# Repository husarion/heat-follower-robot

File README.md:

# Heat Follower

## Description

**Heat Follower** is a project based on the ROSbot Pro platform, that follows heat by using a 360 degree thermal camera. It utilizes a MLX90641 sensor which is a 16x12 pixels IR sensor array. With some custom hardware it is possible to rotate this sensor and get a surround infrared image.

## Hardware

Hardware used in this project:
 - [ROSbot PRO](https://husarion.com/manuals/rosbot/#rosbot-pro)
 - [IR Thermal Sensor Array](https://www.melexis.com/en/product/mlx90641/high-operating-temperature-fir-thermal-sensor-array)
 - [Slip Ring](https://www.sparkfun.com/products/13064)
 - [Custom PCB designed in Eagle](https://github.com/husarion/heat-follower-robot/tree/main/CAD/PCB)
 - [Custom enclosure designed in Fusion 360](https://github.com/husarion/heat-follower-robot/tree/main/CAD)
 
## Software

### Thermal Camera

Software for Thermal Camera is written in [PlatformIO](https://platformio.org/) IDE to ensure compatibility with multiple platforms. MLX90641 [API](https://github.com/melexis/mlx90641-library) is used to ensure proper communication with the IR Sensor. It is slightly modified to support STM32's hardware.
Micro-ROS libraries are mandatory to communicate with ROSbot.

### ROS2 Python Node

A simple Python node was written to process the input thermal image with OpenCV and steer the robot. 
When a heat source is detected, this node sends rotational and linear velocities via `/cmd_vel` topic. 

### ROS Description

 Topic | Node Name | Description 
 --- | --- | ---
 `/thermal_image` | `/thermal_camera` | Raw thermal image represented with grayscale image (temperature = pixel intensity/100). 
 `/tc_image_devel` | `/thermal_subscriber`| Normalized image with target object contours. 
 `/tc_goal_angle` | `/thermal_subscriber`| Arrow marker pointing at the target angle relative to the robot. 
 
Additionally there are 3 parameters

 Parameter | Node Name | Type | Description
 ---  | --- | --- | ---
 `target_min_temp` | `/thermal_subscriber` | int | Minimum temperature of object 
 `target_max_temp` | `/thermal_subscriber` | int | Maximum temperature of object
 `go_to_hottest_piont` | `/thermal_subscriber` | bool | If true, robot follows the hottest object. If false, robot follows object which temperature is within `target_min_temp` and `target_max_temp`.
 
System schematic diagram:

The camera sends the main topic `/thermal_image` - a raw unprocessed image which is then transformed by `/thermal_subscriber` node. The transformed image published on `/tc_image_devel` containes a normalized image with a contour of an object selected by the algorithm. The angle of a selected object can also be visualized with `/tc_goal_angle` marker that publishes an arrow pointing from **base_link** to the direction of the object.

## Building the project

### Flashing MCU

Open the project with [Visual Studio Code](https://code.visualstudio.com/) with [PlatformIO](https://platformio.org/install/ide?install=vscode) plugin.

**This project is optimized for STM32F4 MCU's - keep that in mind when flashing on your hardware!**

After installing the **PlatformIO** extension to your VSCode, click its icon on the **Activity Bar** then from **Project Tasks** select **General** and **Upload**.

### Running on ROSbot

Clone **robot** folder to your ROSbot, connect the Thermal Camera via USB and run
```bash
cd robot/
docker-compose -f docker-compose.yaml up
```
After downloading all the necessary docker images ROSbot should follow warm objects nearby.

Due to issues connected with micro-ros agent, user must **unplug and plug** the Thermal Camera to reset the connection before running the docker compose. 
### Running Rviz on PC

Clone **pc** folder to your PC and run:

```bash
cd pc/
xhost local:root
docker-compose -f compose.pc.yaml up
```

Rviz should now pop up showing ROSbots surroundings in deep infrared.

If images are not visible click **Add** -> **By topic** -> **/thermal_image**

Here's ROSbot facing a kettle:

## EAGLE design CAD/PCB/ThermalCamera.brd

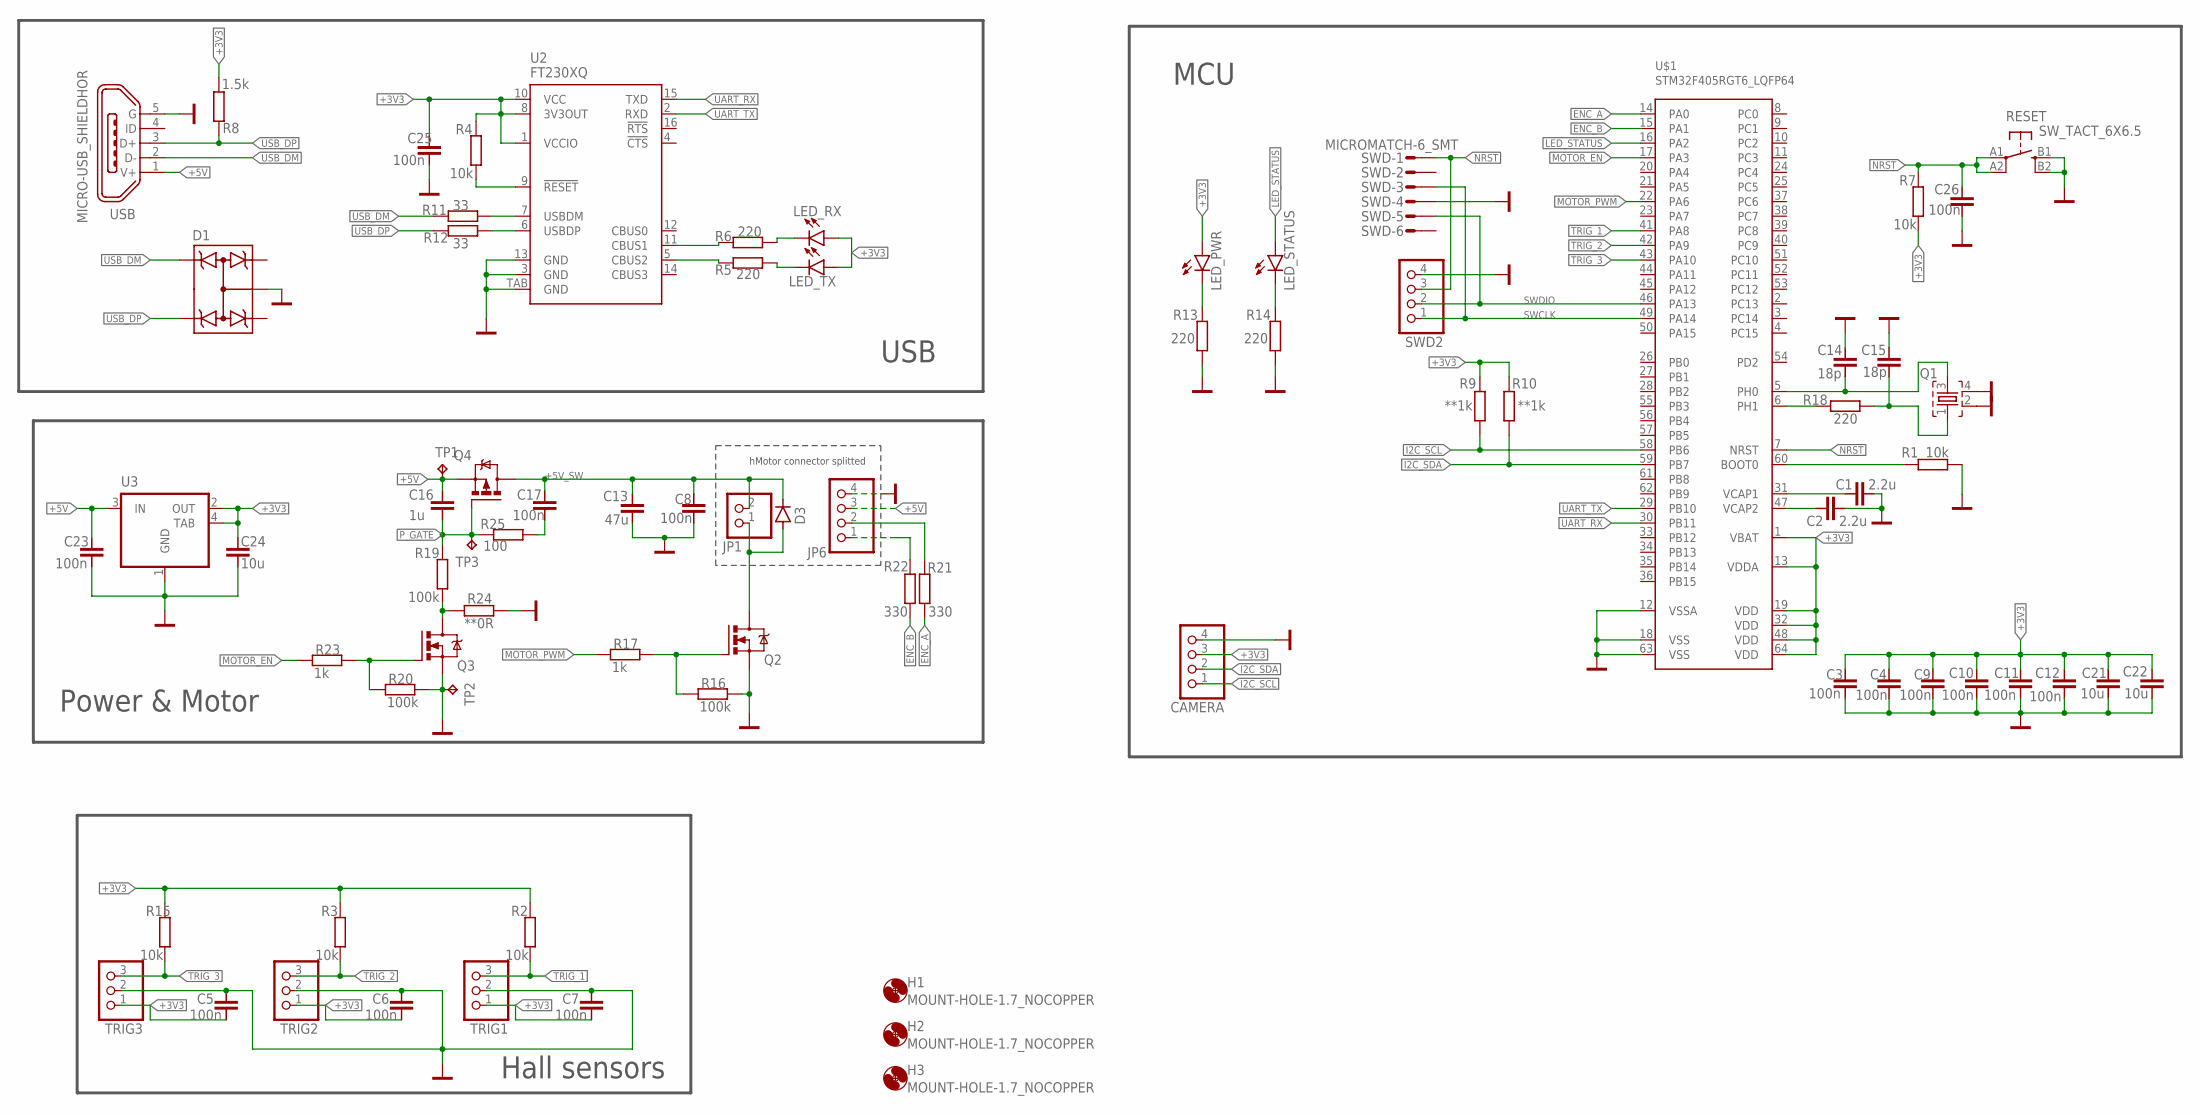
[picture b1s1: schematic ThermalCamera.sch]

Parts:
C1, C2: 2.2u; 0603
C3, C4, C5, C6, C7, C8, C9, C10, C11, C12, C17, C23, C25, C26: 100n; 0603
C13: 47u; 0805
C14, C15: 18p; 0603
C16: 1u; 0603
C21, C22, C24: 10u; 0603
CAMERA: PINHD-1X4; 1X04
D1: TRANSIL-4; SOT323-5
D3: BAR63-03; SOD323
H1, H2, H3: MOUNT-HOLE-1.7_NOCOPPER; 1.7-NO_COPPER
JP1: PINHD-1X2; 1X02
JP6: PINHD-1X4; 1X04
LED_PWR: LEDCHIPLED_0603; CHIPLED_0603
LED_RX: LEDCHIPLED_0603; CHIPLED_0603
LED_STATUS: LEDCHIPLED_0603; CHIPLED_0603
LED_TX: LEDCHIPLED_0603; CHIPLED_0603
Q1: CRYSTAL_4PIN-5X3.2; CRYSTAL_5X3.2_4PIN
Q2, Q3: NMOS-SOT23; SOT23
Q4: PMOS-SOT23; SOT23
R1, R2, R3, R4, R7, R15: 10k; 0603
R5, R6, R13, R14, R18: 220; 0603
R8: 1.5k; 0603
R9, R10: **1k; 0603
R11, R12: 33; 0603
R16, R19, R20: 100k; 0603
R17, R23: 1k; 0603
R21, R22: 330; 0603
R24: **0R; 0603
R25: 100; 0603
RESET: SW_TACT_6X6.5
SWD: MICROMATCH-6_SMT
SWD2: PINHD-1X4; 1X04
TP1, TP2: TPTP12R; TP12R
TP3: TPTP06R; TP06R
TRIG1, TRIG2, TRIG3: PINHD-1X3; 1X03
U2: FT230XQ; QFN16
U3: REG1117; SOT223
U$1: STM32F405RGT6_LQFP64; SQFP-S-10X10-64
USB: MICRO-USB_SHIELDHOR; MICRO_USB_6_SHIELD

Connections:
+3V3: C3.1, C4.1, C5.2, C6.2, C7.2, C9.1, C10.1, C11.1, C12.1, C21.1, C22.1, C24.1, C25.1, CAMERA.3, LED_PWR.A, LED_RX.A, LED_TX.A, R2.2, R3.2, R4.2, R7.1, R8.1, R9.2, R10.2, R15.2, TRIG1.1, TRIG2.1, TRIG3.1, U2.1 (VCCIO), U2.8 (3V3OUT), U2.10 (VCC), U3.2 (OUT), U3.4 (TAB), U$1.1 (VBAT), U$1.13 (VDDA), U$1.19 (VDD), U$1.32 (VDD), U$1.48 (VDD), U$1.64 (VDD)
+5V: C16.1, C23.1, JP6.3, Q4.2 (S), TP1.TP, U3.3 (IN), USB.1 (V+)
+5V_SW: C8.1, C13.1, C17.1, D3.1 (C), JP1.2, Q4.3 (D)
ENC_A: R21.2, U$1.14 (PA0)
ENC_B: R22.1, U$1.15 (PA1)
GND: C1.2, C2.2, C3.2, C4.2, C5.1, C6.1, C7.1, C8.2, C9.2, C10.2, C11.2, C12.2, C13.2, C14.1, C15.1, C21.2, C22.2, C23.2, C24.2, C25.2, C26.2, CAMERA.4, D1.2, JP6.4, Q1.2, Q1.4, Q2.2 (S), Q3.2 (S), R1.2, R13.2, R14.2, R16.1, R20.1, R24.1, RESET.B1 (S), RESET.B2 (S1), SWD.P$4, SWD2.4, TP2.TP, TRIG1.2, TRIG2.2, TRIG3.2, U2.3 (GND), U2.13 (GND), U2.TAB (GND), U3.1 (GND), U$1.12 (VSSA), U$1.18 (VSS), U$1.63 (VSS), USB.5 (G)
I2C_SCL: CAMERA.1, R9.1, U$1.58 (PB6)
I2C_SDA: CAMERA.2, R10.1, U$1.59 (PB7)
LED_STATUS: LED_STATUS.A, U$1.16 (PA2)
MOTOR_EN: R23.2, U$1.17 (PA3)
MOTOR_PWM: R17.2, U$1.22 (PA6)
unnamed: R1.1, U$1.60 (BOOT0)
unnamed: C1.1, U$1.31 (VCAP1)
unnamed: C2.1, U$1.47 (VCAP2)
unnamed: D3.2 (A), JP1.1, Q2.3 (D)
unnamed: R4.1, U2.9 (!RESET)
unnamed: R6.2, U2.11 (CBUS1)
unnamed: R5.2, U2.5 (CBUS2)
unnamed: LED_RX.C, R6.1
unnamed: LED_TX.C, R5.1
unnamed: Q3.3 (D), R19.1, R24.2
unnamed: R11.1, U2.7 (USBDM)
unnamed: R12.1, U2.6 (USBDP)
unnamed: LED_PWR.C, R13.1
unnamed: LED_STATUS.C, R14.1
unnamed: Q2.1 (G), R16.2, R17.1
unnamed: R18.1, U$1.6 (PH1)
unnamed: C15.2, Q1.1, R18.2
unnamed: JP6.2, R21.1
unnamed: C17.2, R25.1
unnamed: Q3.1 (G), R20.2, R23.1
unnamed: JP6.1, R22.2
NRST: C26.1, R7.2, RESET.A1, RESET.A2 (P1), SWD.P$1, SWD2.3, U$1.7 (NRST)
OSC_IN: C14.2, Q1.3, U$1.5 (PH0)
P_GATE: C16.2, Q4.1 (G), R19.2, R25.2, TP3.TP
SWCLK: SWD.P$3, SWD2.1, U$1.49 (PA14)
SWDIO: SWD.P$5, SWD2.2, U$1.46 (PA13)
TRIG_1: R2.1, TRIG1.3, U$1.41 (PA8)
TRIG_2: R3.1, TRIG2.3, U$1.42 (PA9)
TRIG_3: R15.1, TRIG3.3, U$1.43 (PA10)
UART_RX: U2.15 (TXD), U$1.30 (PB11)
UART_TX: U2.2 (RXD), U$1.29 (PB10)
USB_DM: D1.4, R11.2, USB.2 (D-)
USB_DP: D1.5, R8.2, R12.2, USB.3 (D+)

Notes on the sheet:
MCU
Hall sensors
Power & Motor
USB
hMotor connector splitted

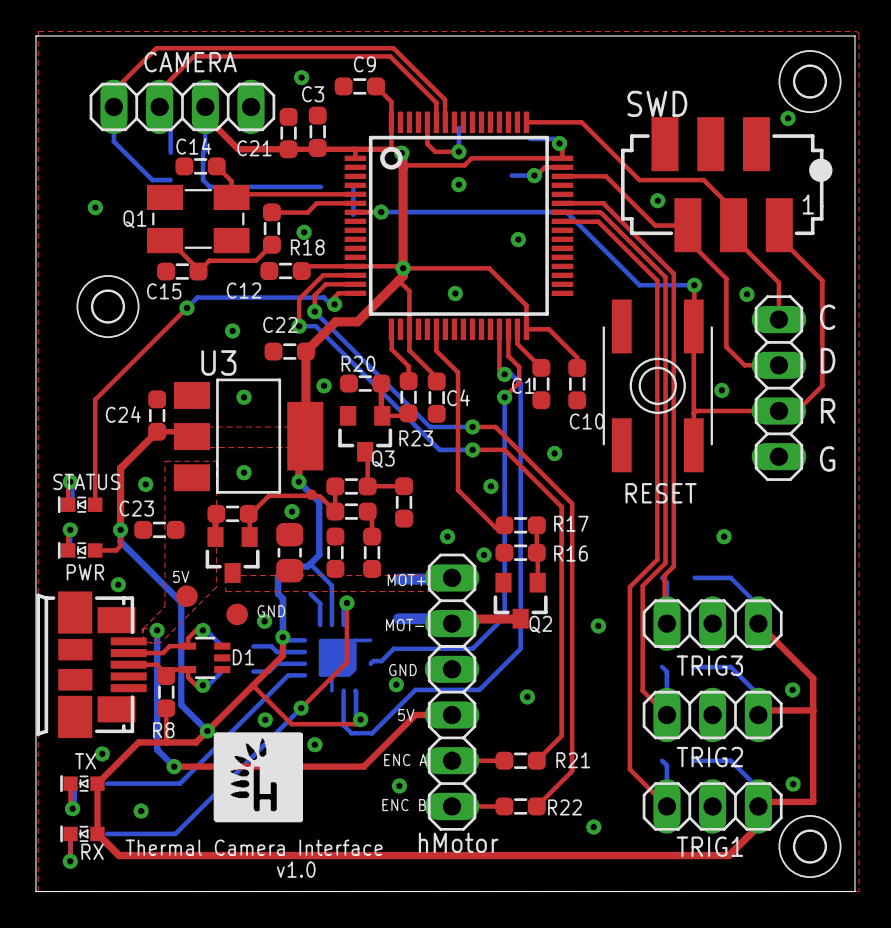
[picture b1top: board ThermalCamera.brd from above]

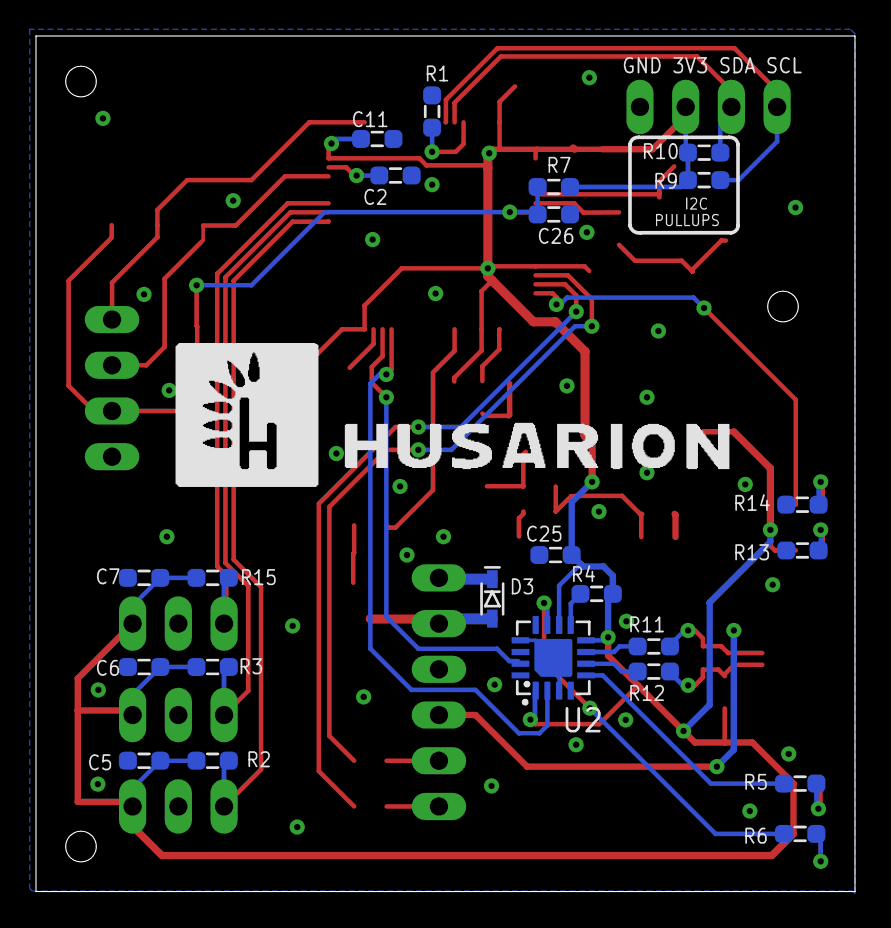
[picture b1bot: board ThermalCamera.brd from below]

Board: 2 copper layers, 45.5 x 47.5 mm, 79 parts (24 on the bottom side), 44 nets.

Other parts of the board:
U$2: HUSARION_SYGNET_5MM
U$3: HUS_NAPIS_BOK_8MM

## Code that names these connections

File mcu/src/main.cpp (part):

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#include "Motor.h"

#define NODE_NAME "Thermal_Camera"
#define LED_PIN PA2
#define MOTOR_PIN PA6
#define IMAGES 3 //number of camera shots per rotation

#define RCCHECK(fn)                \
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  MLX90641_I2CInit();
  Motor_Init();
  pinMode(LED_PIN, OUTPUT);
  pinMode(PA8, INPUT);
  pinMode(PA9, OUTPUT);
  pinMode(PA10, OUTPUT);
  attachInterrupt(PA8, TriggerInterrupt, FALLING);

  //image message definition 
  msg.header.frame_id.data = "map";
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      // MLX90641_TriggerMeasurement(0x33);
      MLX90641_SynchFrame(0x33);
      taskENTER_CRITICAL();
      digitalWrite(PA9, HIGH);  
      vTaskDelay(10);
      MLX90641_GetFrameData(0x33, frameData);
      MLX_Ambient = MLX90641_GetTa(frameData, &MLX_Params);
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
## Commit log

2022-07-06 initial
2022-07-06 added files
2022-07-07 added diagram
2022-07-07 readme update
2022-08-29 Create LICENSE
